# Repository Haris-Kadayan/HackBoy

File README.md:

Hack Boy
-

Hack Boy is a hackpad (macropad) designed to look like the original Game Boy. It has 4 keys, a rotary encoder, an OLED display, and RGB underglow. It is based on QMK firmware and is created for the Hack Club Stasis program.

I made this because I always wanted a macropad for my personal use. However, I did not want it to look like a generic box, so I decided to go with the Game Boy design for it to stand out. It was also a good chance for me to practice my KiCad, Fusion 360, and C skills.

Features
-
* 4x Cherry MX Keys
* 1x EC11 Rotary Encoder
* 1x 0.91" 128x32 OLED Display
* 6x SK2812 MINI-E LEDs
* 1x Seeed Studio XIAO RP2040

CAD
-
I designed the case in Fusion 360. It is a two part case held together using 4 M3 screws and heat set inserts. The deisgn pays homage to the original Game Boy, with realistic grooves, placement, fake buttons, logo, and speaker grille.

Schematic and PCB
-
I designed the schematic and PCB in KiCad. The schematic took the least time. The PCB took much longer. I designed the graphics in Canva and exported it in SVG format. I probably should have added an LED for the top and bottom. Speaking of LEDs, they were a pain to wire, i had to rewire it multiple times to fit all of them. I added holes for allignment but never used them.

Firmware
-
Uses QMK firmware. Here are the functions:
* top left: Copy
* top right: Cut
* encoder press: Mute
* bottom left: Paste
* bottom right: Undo
* encoder turn: Volume up/down

Had some weird compile issue with the LED drivers, but it was fixed with:
WS2812_DRIVER = vendor

BOM:
-
(JLCPCB has a 2 dollar coupon and AliExpress has a 3 dollar coupon, which is why the funding amount is 5 dollars lower than the BOM total):
(not listed in Stasis BOM because I already have these):

* 4x M3x5x5.5 Heat Set Inserts
* 4x M3 Screws

| Name                         | Purpose                         | Quantity | Total Cost (USD) | Link                                                                                                                                                                                                                                                                                                                                                                                                                                                                                                                                                                                                                                                                                                                                                                              | Distributor |
|------------------------------|---------------------------------|----------|------------------|-----------------------------------------------------------------------------------------------------------------------------------------------------------------------------------------------------------------------------------------------------------------------------------------------------------------------------------------------------------------------------------------------------------------------------------------------------------------------------------------------------------------------------------------------------------------------------------------------------------------------------------------------------------------------------------------------------------------------------------------------------------------------------------|-------------|
| 0.91"" 128x32 OLED Display   | Display text and animations     | 1        | 4.07             | https://www.aliexpress.us/item/3256807013199079.html?spm=a2g0o.productlist.main.13.1fb44rbr4rbrJW&algo_pvid=88d61bc3-ad04-48fd-ac39-9cd5ce4a17c7&algo_exp_id=88d61bc3-ad04-48fd-ac39-9cd5ce4a17c7-12&pdp_ext_f=%7B%22order%22%3A%2279%22%2C%22eval%22%3A%221%22%2C%22fromPage%22%3A%22search%22%7D&pdp_npi=6%40dis%21USD%214.09%213.59%21%21%2127.64%2124.26%21%40210337c117794986562357406e71c3%2112000046316668326%21sea%21US%210%21ABX%211%210%21n_tag%3A-29910%3Bd%3A8f9e3ac0%3Bm03_new_user%3A-29895%3BpisId%3A5000000204886261&curPageLogUid=ILeZHAD4BSke&utparam-url=scene%3Asearch%7Cquery_from%3A%7Cx_object_id%3A1005007199513831%7C_p_origin_prod%3A                                                                                                                   | AliExpress  |
| 10 PCS DSA Black Keycaps     | Covers the key switches         | 1        | 2.7              | https://www.aliexpress.us/item/3256810533781399.html?spm=a2g0o.productlist.main.2.76barKVkrKVkw8&algo_pvid=a0e25742-d517-49cf-90b6-502203a18787&algo_exp_id=a0e25742-d517-49cf-90b6-502203a18787-1&pdp_ext_f=%7B%22order%22%3A%22586%22%2C%22eval%22%3A%221%22%2C%22fromPage%22%3A%22search%22%7D&pdp_npi=6%40dis%21USD%212.66%212.16%21%21%212.66%212.16%21%402103123917794978454482320eb10c%2112000053290823995%21sea%21US%210%21ABX%211%210%21n_tag%3A-29910%3Bd%3A8f9e3ac0%3Bm03_new_user%3A-29895%3BpisId%3A5000000204886261&curPageLogUid=EOFkWa1pLd43&utparam-url=scene%3Asearch%7Cquery_from%3A%7Cx_object_id%3A1005010720096151%7C_p_origin_prod%3A                                                                                                                      | AliExpress  |
| PCB                          | Connects all the components     | 1        | 2                | https://cart.jlcpcb.com/quote?stencilLayer=2&stencilWidth=100&stencilLength=100&stencilCounts=5&plateType=1&spm=Jlcpcb.Homepage.1010                                                                                                                                                                                                                                                                                                                                                                                                                                                                                                                                                                                                                                              | JLCPCB      |
| SK6812-E MINI-E LEDs         | Lights up the macropad          | 1        | 2.43             | https://www.aliexpress.us/item/3256805007401420.html?src=google&src=google&albch=shopping&acnt=708-803-3821&isdl=y&slnk=&plac=&mtctp=&albbt=Google_7_shopping&aff_platform=google&aff_short_key=UneMJZVf&gclsrc=aw.ds&albagn=888888&ds_e_adid=&ds_e_matchtype=&ds_e_device=c&ds_e_network=x&ds_e_product_group_id=&ds_e_product_id=en3256805007401420&ds_e_product_merchant_id=579408549&ds_e_product_country=US&ds_e_product_language=en&ds_e_product_channel=online&ds_e_product_store_id=&ds_url_v=2&albcp=19419176312&albag=&isSmbAutoCall=false&needSmbHouyi=false&gad_source=1&gad_campaignid=19419169321&gbraid=0AAAAAD6I-hEZe85gq6SaAjufh59rQoHQC&gclid=Cj0KCQjwyr3OBhD0ARIsALlo-Om1MU1fzzwNndIHXdMPar71GHYK74SMb5pBdOySu_c3fGzl6F0mJQQaAlrfEALw_wcB&gatewayAdapt=glo2usa | AliExpress  |
| EC11 Rotary Encoder 5 PCS    | Input knob                      | 1        | 3.24             | https://www.aliexpress.us/item/3256808530463909.html?spm=a2g0o.detail.0.0.51b99wd09wd0fl&mp=1&pdp_npi=6%40dis%21USD%21USD+3.31%21USD+2.80%21%21USD+2.80%21%21%21%40210311a017794977756083026e4b30%2112000046368783803%21ct%21US%21-1%21%211%210%21&_gl=1*1pwpes3*_gcl_aw*R0NMLjE3Nzk0OTc1MzMuQ2owS0NRand5cjNPQmhEMEFSSXNBTGxvLU9tMU1VMWZ6endObmRJSFhkTVBhcjcxR0hZSzc0U01iNXBCZE95U3VfYzNmR3psNkYwbUpRUWFBbHJmRUFMd193Y0I.*_gcl_dc*R0NMLjE3Nzk0OTc1MzMuQ2owS0NRand5cjNPQmhEMEFSSXNBTGxvLU9tMU1VMWZ6endObmRJSFhkTVBhcjcxR0hZSzc0U01iNXBCZE95U3VfYzNmR3psNkYwbUpRUWFBbHJmRUFMd193Y0I.*_gcl_au*NDUyODkyMjcxLjE3Nzk0OTM2MTE.*_ga*MTY1MzkyNjEyMi4xNzc1MjgwMTA1*_ga_VED1YSGNC7*czE3Nzk0OTcyNjUkbzQkZzEkdDE3Nzk0OTc3NzUkajQ5JGwwJGgw&gatewayAdapt=glo2usa                                 | AliExpress  |
| 20 PCS Brown Switch          | Input button                    | 1        | 0.99             | https://www.aliexpress.us/item/3256811652574937.html?spm=a2g0o.cart.0.0.14fc7a9dFa3X1v&mp=1&pdp_npi=6%40dis%21USD%21USD+2.99%21USD+0.99%21%21USD+0.99%21%21%21%402101eecd17809377910832251e98ce%2112000056744509269%21ct%21US%217700223557%21%211%210%21&_gl=1*1q92loc*_gcl_aw*R0NMLjE3Nzk0OTc1MzMuQ2owS0NRand5cjNPQmhEMEFSSXNBTGxvLU9tMU1VMWZ6endObmRJSFhkTVBhcjcxR0hZSzc0U01iNXBCZE95U3VfYzNmR3psNkYwbUpRUWFBbHJmRUFMd193Y0I.*_gcl_dc*R0NMLjE3Nzk0OTc1MzMuQ2owS0NRand5cjNPQmhEMEFSSXNBTGxvLU9tMU1VMWZ6endObmRJSFhkTVBhcjcxR0hZSzc0U01iNXBCZE95U3VfYzNmR3psNkYwbUpRUWFBbHJmRUFMd193Y0I.*_gcl_au*NDUyODkyMjcxLjE3Nzk0OTM2MTE.*_ga*NzY5NTYyMDc3LjE3ODA4NTI1MDc.*_ga_VED1YSGNC7*czE3ODA5Mzc3ODMkbzIkZzEkdDE3ODA5Mzc3OTMkajUwJGwwJGgw&gatewayAdapt=glo2usa                           | AliExpress  |
| Seeed Studio XIAO RP2040     | Controls the macropad           | 1        | 9.99             | https://www.amazon.com/Microcontroller-Dual-Core-MicroPython-CircuitPython-Interfaces/dp/B09NNVNW7M/ref=sr_1_1?crid=11LJQMLOUBNZL&dib=eyJ2IjoiMSJ9.Hxs3jCHqokIXwzSfDn6Q00dVyEjPI8sSxCsrRDHxt6c7Cg-4TTc6FHlM9xT0HpXQH3fLkjPcXW9UDjBryk2urLUt4DOboVISIgcR7C__JJletdZ9K-Dsz5KXHpiEhaYvu9m14HIzAKxgRISDl-DlLk2jcXUuy38YGKEVhK0URi_xmgbK2VdKH5aG_duyvRQe595QZFTSHVnM5yZ7HMzDXfyUofMHRuGhclG-i31LKjE.cjAjLB-Wy8Puj3evec66X3kp8MaTCKanFVZYivxmDsI&dib_tag=se&keywords=seeed%2Bstudio%2Bxiao%2Brp2040&qid=1775279587&sprefix=seeed%2Bstudio%2Bxiao%2Brp%2Caps%2C1054&sr=8-1&th=1                                                                                                                                                                                                          | Amazon      |
| 4x M3x5x5.5 Heat Set Inserts | Where the M3 screws thread into | 1        | Already own      |                                                                                                                                                                                                                                                                                                                                                                                                                                                                                                                                                                                                                                                                                                                                                                                   |             |
| 4x M3 Screws                 | To attach the body and lid      | 1        | Already own      |                                                                                                                                                                                                                                                                                                                                                                                                                                                                                                                                                                                                                                                                                                                                                                                   |             |

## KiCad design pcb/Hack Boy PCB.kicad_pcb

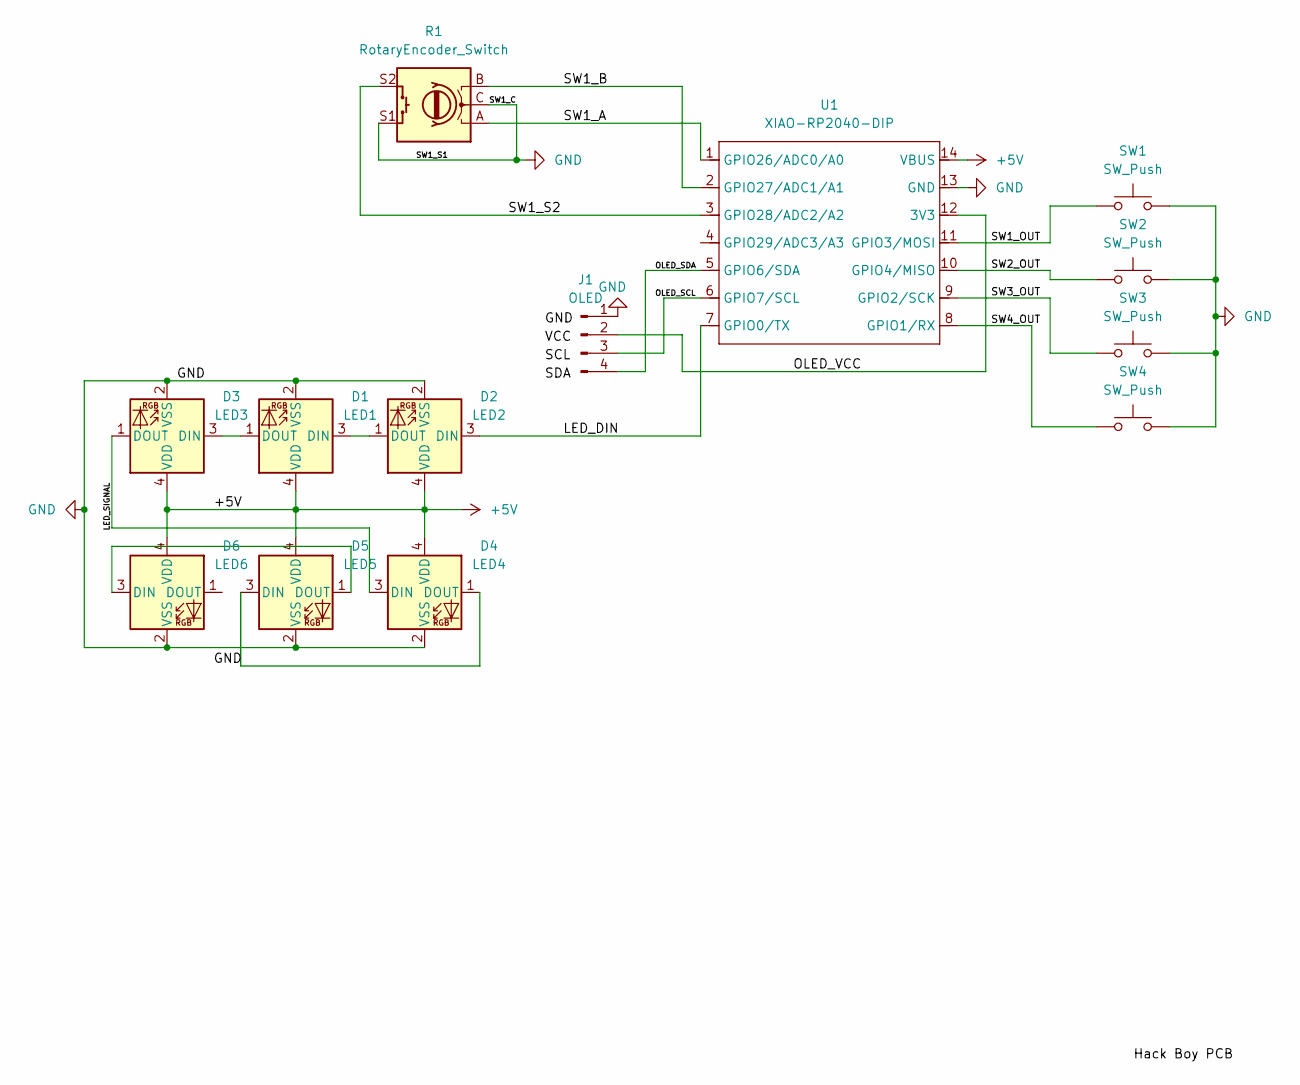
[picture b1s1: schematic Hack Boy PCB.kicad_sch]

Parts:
D1: LED1; SK6812MINI-E_fixed
D2: LED2; SK6812MINI-E_fixed
D3: LED3; SK6812MINI-E_fixed
D4: LED4; SK6812MINI-E_fixed
D5: LED5; SK6812MINI-E_fixed
D6: LED6; SK6812MINI-E_fixed
J1: OLED; SSD1306-0.91-OLED-4pin-128x32
R1: RotaryEncoder_Switch; RotaryEncoder_Alps_EC11E-Switch_Vertical_H20mm
SW1, SW2, SW3, SW4: SW_Push; SW_Cherry_MX_1.00u_PCB
U1: XIAO-RP2040-DIP

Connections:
+5V: D1.4 (VDD), D2.4 (VDD), D3.4 (VDD), D4.4 (VDD), D5.4 (VDD), D6.4 (VDD), U1.14 (VBUS)
/LED_DIN: D2.3 (DIN), U1.7 (GPIO0/TX)
/LED_SIGNAL: D3.1 (DOUT), D4.3 (DIN)
/OLED_SDA: J1.4, U1.5 (GPIO6/SDA)
/OLED_VCC: J1.2, U1.12 (3V3)
/SW1_A: R1.A, U1.1 (GPIO26/ADC0/A0)
/SW1_B: R1.B, U1.2 (GPIO27/ADC1/A1)
/SW1_OUT: SW1.1, U1.11 (GPIO3/MOSI)
/SW1_S2: R1.S2, U1.3 (GPIO28/ADC2/A2)
/SW2_OUT: SW2.1, U1.10 (GPIO4/MISO)
/SW3_OUT: SW3.1, U1.9 (GPIO2/SCK)
GND: D1.2 (VSS), D2.2 (VSS), D3.2 (VSS), D4.2 (VSS), D5.2 (VSS), D6.2 (VSS), J1.1, R1.C, R1.S1, SW1.2, SW2.2, SW3.2, SW4.2, U1.13 (GND)
unnamed: D1.3 (DIN), D2.1 (DOUT)
unnamed: D1.1 (DOUT), D3.3 (DIN)
unnamed: D4.1 (DOUT), D5.3 (DIN)
unnamed: D5.1 (DOUT), D6.3 (DIN)
unnamed: J1.3, U1.6 (GPIO7/SCL)
unnamed: SW4.1, U1.8 (GPIO1/RX)

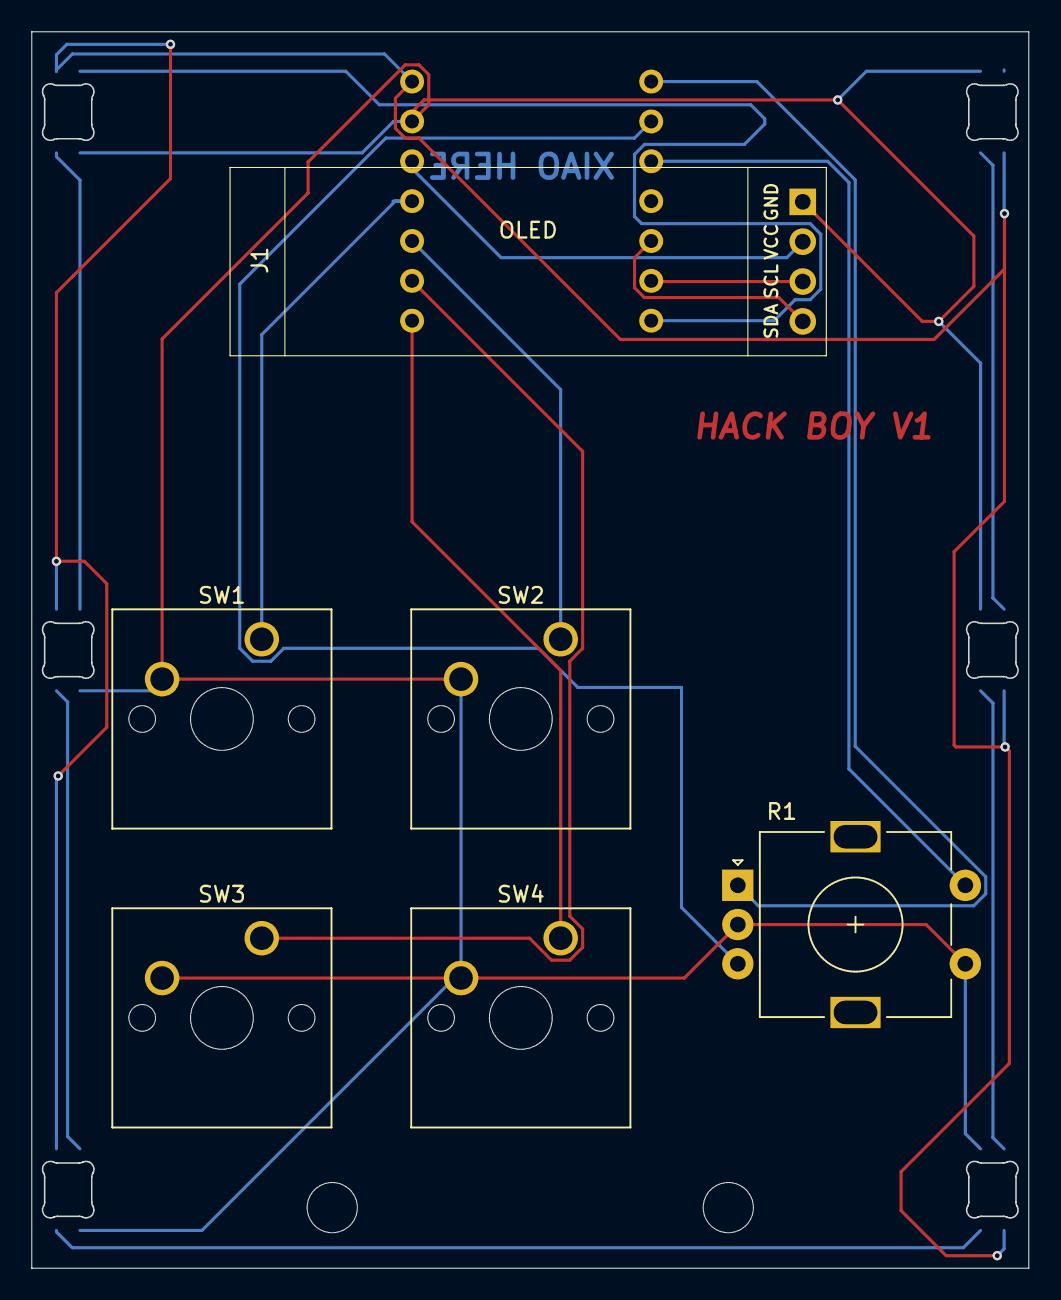
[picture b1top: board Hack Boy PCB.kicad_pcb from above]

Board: 2 copper layers, 63.5 x 78.8 mm, 14 parts (1 on the bottom side), 18 nets.

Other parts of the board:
REF: AlignHole_1p6mm

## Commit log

2026-04-07 Enhance README with detailed project information
    Expanded the README to include detailed information about the Hack Boy, its features, CAD design, schematic and PCB design, firmware functions, and BOM.
2026-04-09 Revise README introduction for clarity
    Removed the introductory greeting from the README.
2026-05-17 Rename Hack Boy Assembly.zip to Hack Boy Assembly STEP.zip
2026-05-17 Rename Hack Boy Enclosure.zip to Hack Boy Enclosure f3z.zip
2026-05-17 Update README with image and project details
    Added an image and enhanced the project description.
2026-05-17 Fix duplicate image tag in README.md
    Removed duplicate image tag from README.
2026-05-17 Add CAD files with Git LFS
2026-05-23 Update BOM section in README.md
    Removed specific BOM items that are no longer needed.
2026-05-23 Update BOM section with coupon information
